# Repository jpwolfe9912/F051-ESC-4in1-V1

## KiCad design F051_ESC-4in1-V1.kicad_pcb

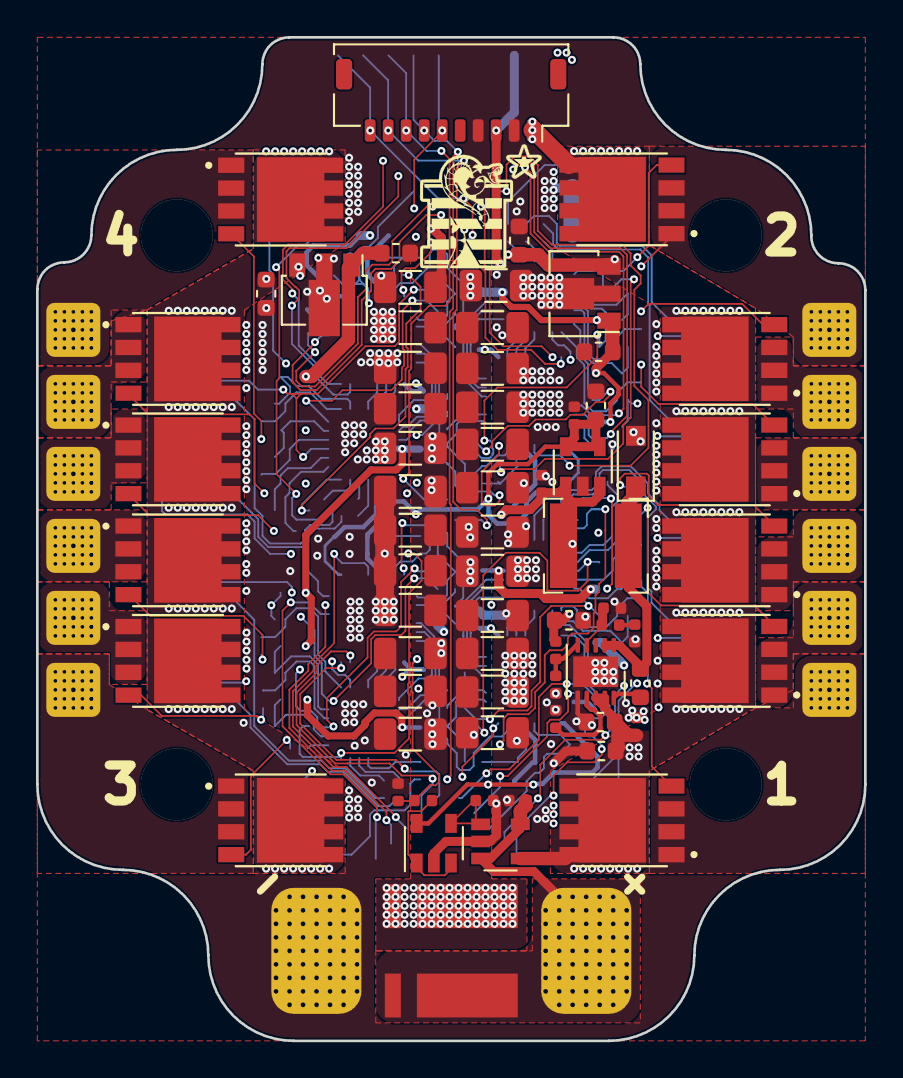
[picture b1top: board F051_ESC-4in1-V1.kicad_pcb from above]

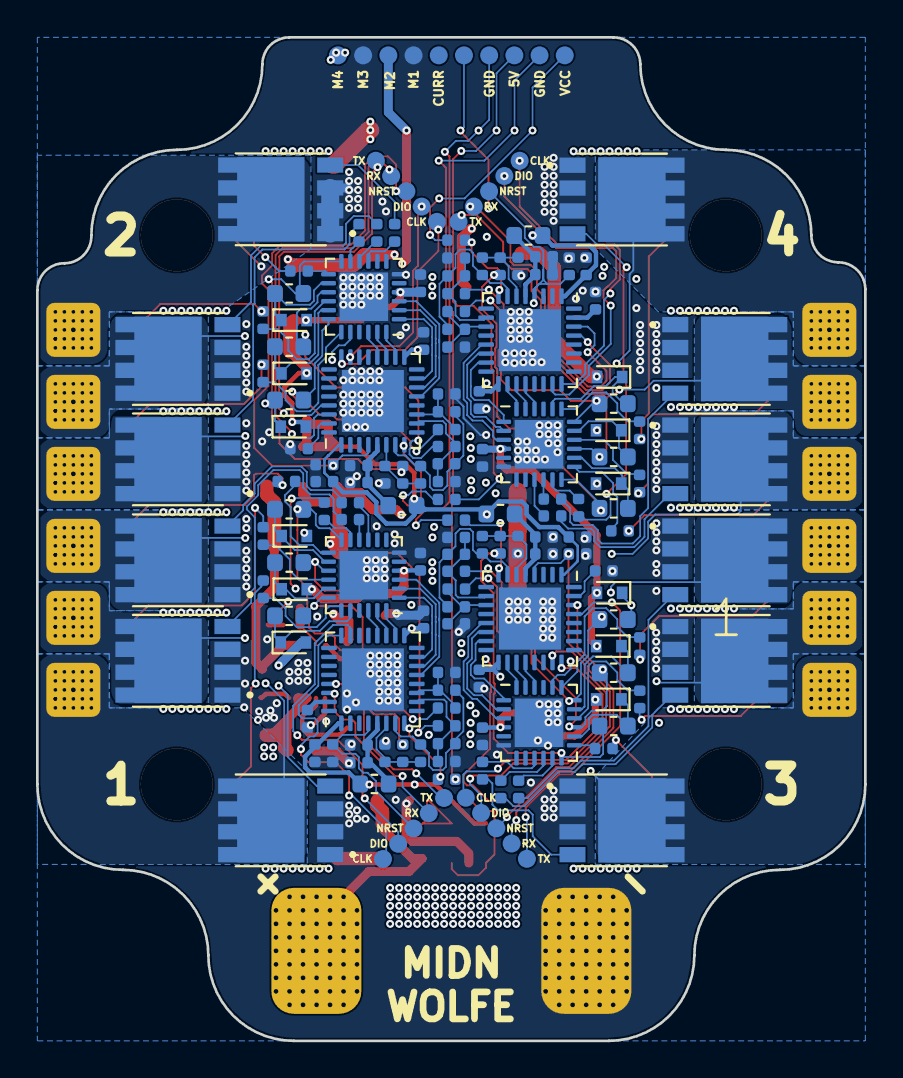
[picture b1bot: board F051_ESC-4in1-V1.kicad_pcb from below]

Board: 4 copper layers, 46.0 x 55.8 mm, 222 parts (147 on the bottom side), 164 nets.

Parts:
C1, C23, C27, C32, C41: 10nF; C_0402_1005Metric
C2, C22, C28, C33, C42: 1uF; C_0402_1005Metric
C3, C6, C7, C9, C11, C12, C29, C30, C31, C34, C35, C36, C37, C43, C44, C45, C46, C74: 0.1uF; C_0402_1005Metric
C4, C68: 0.33uF; C_0603_1608Metric
C5, C10, C13, C14, C15, C25, C26, C38, C39, C40, C47, C48, C49, C69, C70: 0.1uF; C_0603_1608Metric
C8: 3.3nF; C_0402_1005Metric
C16, C17, C18, C19, C20, C21, C50, C51, C52, C53, C54, C55, C56, C57, C58, C59, C60, C61, C62, C63, C64, C65, C66, C67: 0.1uF; C_1206_3216Metric
C24, C72, C73: 2.2uF; C_0603_1608Metric
C71: 22uF; C_0603_1608Metric
C75: 560pF; C_0402_1005Metric
C76: 2pF; C_0402_1005Metric
D1, D2, D3, D4, D5, D6, D7, D8, D9, D10, D11, D12: 250V; D_SOD-523
D13: 50V, 2A; D_SOD-123F
FB1, FB2, FB3, FB4: 100@100MHz; L_0603_1608Metric
H1, H2, H3, H4: MountingHole_Pad; MountingHole_4in1ESC
J1: Conn_01x02; Conn_PowerPad_4in1
J2: Conn_01x10; JST_SHL_SM10B-SHLS-TF_1x10-1MP_P1.00mm_Horizontal
J3, J4, J5, J7: Conn_01x05; Conn_Debug
J6, J8, J11, J14: Conn_01x03; Conn_MotorPhase
J9: Conn_01x10; Conn_FC_Solder_10
L1: L_Small; L_Bourns-SRN5020
Q1, Q2, Q3, Q4, Q5, Q6, Q7, Q8, Q9, Q10, Q11, Q12, Q13, Q14, Q15, Q16, Q17, Q18, Q19, Q20, Q21, Q22, Q23, Q24: TPHR8504PL
R1: 0m50; R_Shunt_Vishay_WSLP2726
R2: 60k; R_0402_1005Metric
R3: 500; R_0402_1005Metric
R4, R5, R6, R18, R19, R20, R21, R22, R23, R24, R25, R26, R49, R50, R51, R52, R53, R54, R66, R67, R68, R69, R70, R71: 10; R_0402_1005Metric
R7, R8, R9, R10, R12, R13, R27, R28, R29, R30, R32, R33, R38, R39, R40, R41, R43, R44, R55, R56, R57, R58, R60, R61: 10k; R_0402_1005Metric
R11, R14, R15, R16, R17, R31, R34, R35, R36, R37, R42, R45, R46, R47, R48, R59, R62, R63, R64, R65: 1k; R_0402_1005Metric
R73: 20k; R_0402_1005Metric
R74: 3.8k; R_0402_1005Metric
R76: 200k; R_0402_1005Metric
R77: 68k; R_0402_1005Metric
U1, U8, U9, U11: STM32F051K6Ux; QFN-32-1EP_5x5mm_P0.5mm_EP3.45x3.45mm
U2, U6, U10, U12: FD6288Q; QFN-24-1EP_4x4mm_P0.5mm_EP2.7x2.7mm
U3, U13: L78L12_SOT89; SOT-89-3
U4: LP2985-3.3; SOT-23-5
U5: INA139; SOT-23-5
U7: OPA340NA; SOT-23-5
U14: MP4560_QFN10; DFN-10-1EP_3x3mm_P0.5mm_EP1.7x2.5mm

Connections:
+3.3VA_1: C1.1, C2.1, FB1.1, U1.5
+3.3VA_2: C27.1, C28.1, FB2.1, U8.5
+3.3VA_3: C32.1, C33.1, FB3.1, U9.5
+3.3VA_4: C41.1, C42.1, FB4.1, U11.5
+3V3: C3.1, C6.1, C23.1, C24.1, C29.1, C30.1, C34.1, C35.1, C43.1, C44.1, FB1.2, FB2.2, FB3.2, FB4.2, U1.1, U1.17, U4.4, U4.5, U7.5, U8.1, U8.17, U9.1, U9.17, U11.1, U11.17
+5V: C22.1, C71.1, J2.3, J9.3, L1.2, R73.1, U4.1, U4.3
+12V_1: C37.1, C46.1, C69.1, D7.2, D8.2, D9.2, D10.2, D11.2, D12.2, U10.4, U12.4, U13.1
+12V_2: C5.1, C9.1, C12.1, D1.2, D2.2, D3.2, D4.2, D5.2, D6.2, U2.4, U3.1, U6.4
/Curent Sense/CURR: C8.2, J2.6, J9.6, R3.1
/MCU 1/BOOT0: R17.1, U1.31
/MCU 1/HIN1: U1.18, U2.24
/MCU 1/HIN2: U1.19, U2.23
/MCU 1/LIN1: U1.15, U2.1
/MCU 1/LIN2: U1.14, U2.2
/MCU 1/LIN3: U1.13, U2.3
/MCU 1/NRST: C11.1, J3.3, U1.4
/MCU 1/PhaseA: C13.2, J6.3, Q1.1, Q1.2, Q1.3, Q2.5, Q2.6, Q2.7, Q2.8, Q2.9, R7.2, U2.18
/MCU 1/PhaseB: C14.2, J6.2, Q3.1, Q3.2, Q3.3, Q4.5, Q4.6, Q4.7, Q4.8, Q4.9, R9.2, U2.15
/MCU 1/PhaseC: C15.2, J6.1, Q5.1, Q5.2, Q5.3, Q6.5, Q6.6, Q6.7, Q6.8, Q6.9, R12.2, U2.12
/MCU 1/SWCLK: J3.1, U1.24
/MCU 1/SWDIO: J3.2, U1.23
/MCU 1/SenseA: R7.1, R8.1, R14.2, U1.11
/MCU 1/SenseB: R9.1, R10.1, R15.2, U1.10
/MCU 1/SenseC: R12.1, R13.1, R16.2, U1.6
/MCU 1/SenseCOM: R8.2, R10.2, R13.2, U1.7
/MCU 1/USART1_RX: J3.4, U1.30
/MCU 1/USART1_TX: J3.5, U1.29
/MCU 2/BOOT0: R37.1, U8.31
/MCU 2/HIN1: U6.24, U8.18
/MCU 2/HIN2: U6.23, U8.19
/MCU 2/LIN1: U6.1, U8.15
/MCU 2/LIN2: U6.2, U8.14
/MCU 2/LIN3: U6.3, U8.13
/MCU 2/NRST: C31.1, J5.3, U8.4
/MCU 2/PhaseA: C10.2, J8.3, Q7.1, Q7.2, Q7.3, Q8.5, Q8.6, Q8.7, Q8.8, Q8.9, R27.2, U6.18
/MCU 2/PhaseB: C25.2, J8.2, Q9.1, Q9.2, Q9.3, Q10.5, Q10.6, Q10.7, Q10.8, Q10.9, R29.2, U6.15
/MCU 2/PhaseC: C26.2, J8.1, Q11.1, Q11.2, Q11.3, Q12.5, Q12.6, Q12.7, Q12.8, Q12.9, R32.2, U6.12
/MCU 2/SWCLK: J5.1, U8.24
/MCU 2/SWDIO: J5.2, U8.23
/MCU 2/SenseA: R27.1, R28.1, R34.2, U8.11
/MCU 2/SenseB: R29.1, R30.1, R35.2, U8.10
/MCU 2/SenseC: R32.1, R33.1, R36.2, U8.6
/MCU 2/SenseCOM: R28.2, R30.2, R33.2, U8.7
/MCU 2/USART1_RX: J5.4, U8.30
/MCU 2/USART1_TX: J5.5, U8.29
/MCU 3/BOOT0: R48.1, U9.31
/MCU 3/HIN1: U9.18, U10.24
/MCU 3/HIN2: U9.19, U10.23
/MCU 3/LIN1: U9.15, U10.1
/MCU 3/LIN2: U9.14, U10.2
/MCU 3/LIN3: U9.13, U10.3
/MCU 3/NRST: C36.1, J4.3, U9.4
/MCU 3/PhaseA: C38.2, J11.3, Q13.1, Q13.2, Q13.3, Q14.5, Q14.6, Q14.7, Q14.8, Q14.9, R38.2, U10.18
/MCU 3/PhaseB: C39.2, J11.2, Q15.1, Q15.2, Q15.3, Q16.5, Q16.6, Q16.7, Q16.8, Q16.9, R40.2, U10.15
/MCU 3/PhaseC: C40.2, J11.1, Q17.1, Q17.2, Q17.3, Q18.5, Q18.6, Q18.7, Q18.8, Q18.9, R43.2, U10.12
/MCU 3/SWCLK: J4.1, U9.24
/MCU 3/SWDIO: J4.2, U9.23
/MCU 3/SenseA: R38.1, R39.1, R45.2, U9.11
/MCU 3/SenseB: R40.1, R41.1, R46.2, U9.10
/MCU 3/SenseC: R43.1, R44.1, R47.2, U9.6
/MCU 3/SenseCOM: R39.2, R41.2, R44.2, U9.7
/MCU 3/USART1_RX: J4.4, U9.30
/MCU 3/USART1_TX: J4.5, U9.29
/MCU 4/BOOT0: R65.1, U11.31
/MCU 4/HIN1: U11.18, U12.24
/MCU 4/HIN2: U11.19, U12.23
/MCU 4/LIN1: U11.15, U12.1
/MCU 4/LIN2: U11.14, U12.2
/MCU 4/LIN3: U11.13, U12.3
/MCU 4/NRST: C45.1, J7.3, U11.4
/MCU 4/PhaseA: C47.2, J14.3, Q19.1, Q19.2, Q19.3, Q20.5, Q20.6, Q20.7, Q20.8, Q20.9, R55.2, U12.18
/MCU 4/PhaseB: C48.2, J14.2, Q21.1, Q21.2, Q21.3, Q22.5, Q22.6, Q22.7, Q22.8, Q22.9, R57.2, U12.15
/MCU 4/PhaseC: C49.2, J14.1, Q23.1, Q23.2, Q23.3, Q24.5, Q24.6, Q24.7, Q24.8, Q24.9, R60.2, U12.12
/MCU 4/SWCLK: J7.1, U11.24
/MCU 4/SWDIO: J7.2, U11.23
/MCU 4/SenseA: R55.1, R56.1, R62.2, U11.11
/MCU 4/SenseB: R57.1, R58.1, R63.2, U11.10
/MCU 4/SenseC: R60.1, R61.1, R64.2, U11.6
/MCU 4/SenseCOM: R56.2, R58.2, R61.2, U11.7
/MCU 4/USART1_RX: J7.4, U11.30
/MCU 4/USART1_TX: J7.5, U11.29
/MOSFET Driver 1/HIN1: U1.20, U2.22
/MOSFET Driver 1/HO1: R18.2, U2.19
/MOSFET Driver 1/HO2: R20.2, U2.16
/MOSFET Driver 1/HO3: R23.2, U2.13
/MOSFET Driver 1/LO1: R19.2, U2.11
/MOSFET Driver 1/LO2: R21.2, U2.10
/MOSFET Driver 1/LO3: R24.2, U2.9
/MOSFET Driver 1/VB1: C13.1, D2.1, U2.20
/MOSFET Driver 1/VB2: C14.1, D3.1, U2.17
/MOSFET Driver 1/VB3: C15.1, D4.1, U2.14
/MOSFET Driver 2/HIN1: U6.22, U8.20
/MOSFET Driver 2/HO1: R4.2, U6.19
/MOSFET Driver 2/HO2: R6.2, U6.16
/MOSFET Driver 2/HO3: R25.2, U6.13
/MOSFET Driver 2/LO1: R5.2, U6.11
/MOSFET Driver 2/LO2: R22.2, U6.10
/MOSFET Driver 2/LO3: R26.2, U6.9
/MOSFET Driver 2/VB1: C10.1, D1.1, U6.20
/MOSFET Driver 2/VB2: C25.1, D5.1, U6.17
/MOSFET Driver 2/VB3: C26.1, D6.1, U6.14
/MOSFET Driver 3/HIN1: U9.20, U10.22
/MOSFET Driver 3/HO1: R49.2, U10.19
/MOSFET Driver 3/HO2: R51.2, U10.16
/MOSFET Driver 3/HO3: R53.2, U10.13
/MOSFET Driver 3/LO1: R50.2, U10.11
/MOSFET Driver 3/LO2: R52.2, U10.10
/MOSFET Driver 3/LO3: R54.2, U10.9
/MOSFET Driver 3/VB1: C38.1, D7.1, U10.20
/MOSFET Driver 3/VB2: C39.1, D8.1, U10.17
/MOSFET Driver 3/VB3: C40.1, D9.1, U10.14
/MOSFET Driver 4/HIN1: U11.20, U12.22
/MOSFET Driver 4/HO1: R66.2, U12.19
/MOSFET Driver 4/HO2: R68.2, U12.16
/MOSFET Driver 4/HO3: R70.2, U12.13
/MOSFET Driver 4/LO1: R67.2, U12.11
/MOSFET Driver 4/LO2: R69.2, U12.10
/MOSFET Driver 4/LO3: R71.2, U12.9
/MOSFET Driver 4/VB1: C47.1, D10.1, U12.20
/MOSFET Driver 4/VB2: C48.1, D11.1, U12.17
/MOSFET Driver 4/VB3: C49.1, D12.1, U12.14
/PWM_1: J2.7, J9.7, R11.2
/PWM_2: J2.8, J9.8, R31.2
/PWM_3: J2.9, J9.9, R42.2
/PWM_4: J2.10, J9.10, R59.2
GND: C1.2, C2.2, C3.2, C4.2, C5.2, C6.2, C7.1, C8.1, C9.2, C11.2, C12.2, C16.1, C17.1, C18.1, C19.1, C20.1, C21.1, C22.2, C23.2, C24.2, C27.2, C28.2, C29.2, C30.2, C31.2, C32.2, C33.2, C34.2, C35.2, C36.2, C37.2, C41.2, C42.2, C43.2, C44.2, C45.2, C46.2, C50.1, C51.1, C52.1, C53.1, C54.1, C55.1, C56.1, C57.1, C58.1, C59.1, C60.1, C61.1, C62.1, C63.1, C64.1, C65.1, C66.1, C67.1, C68.2, C69.2, C71.2, C72.2, C73.2, C74.2, C76.2, D13.2, H1.1, H2.1, H3.1, H4.1, J1.2, J2.2, J2.4, J9.2, J9.4, Q2.1, Q2.2, Q2.3, Q4.1, Q4.2, Q4.3, Q6.1, Q6.2, Q6.3, Q8.1, Q8.2, Q8.3, Q10.1, Q10.2, Q10.3, Q12.1, Q12.2, Q12.3, Q14.1, Q14.2, Q14.3, Q16.1, Q16.2, Q16.3, Q18.1, Q18.2, Q18.3, Q20.1, Q20.2, Q20.3, Q22.1, Q22.2, Q22.3, Q24.1, Q24.2, Q24.3, R2.2, R14.1, R15.1, R16.1, R17.2, R34.1, R35.1, R36.1, R37.2, R45.1, R46.1, R47.1, R48.2, R62.1, R63.1, R64.1, R65.2, R74.2, R76.2, R77.2, U1.33, U2.6, U2.25, U3.2, U4.2, U5.2, U6.6, U6.25, U7.2, U8.33, U9.33, U10.6, U10.25, U11.33, U12.6, U12.25, U13.2, U14.6
unnamed: C70.1, D13.1, L1.1, U14.1, U14.2
unnamed: C70.2, U14.10
unnamed: C75.1, C76.1, U14.4
unnamed: C75.2, R77.1
unnamed: Q1.4, R18.1
unnamed: Q2.4, R19.1
unnamed: Q3.4, R20.1
unnamed: Q4.4, R21.1
unnamed: Q5.4, R23.1
unnamed: Q6.4, R24.1
unnamed: Q7.4, R4.1
unnamed: Q8.4, R5.1
unnamed: Q9.4, R6.1
unnamed: Q10.4, R22.1
unnamed: Q11.4, R25.1
unnamed: Q12.4, R26.1
unnamed: Q13.4, R49.1
unnamed: Q14.4, R50.1
unnamed: Q15.4, R51.1
unnamed: Q16.4, R52.1
unnamed: Q17.4, R53.1
unnamed: Q18.4, R54.1
unnamed: Q19.4, R66.1
unnamed: Q20.4, R67.1
unnamed: Q21.4, R68.1
unnamed: Q22.4, R69.1
unnamed: Q23.4, R70.1
unnamed: Q24.4, R71.1
unnamed: R2.1, U5.1, U7.4
unnamed: R3.2, U7.1, U7.3
unnamed: R11.1, U1.8
unnamed: R31.1, U8.8
unnamed: R42.1, U9.8
unnamed: R59.1, U11.8
unnamed: R73.2, R74.1, U14.5
unnamed: R76.1, U14.7
VCC: C7.2, J1.1, R1.1, U5.3, U5.5
VCC_Shunt: C4.1, C16.2, C17.2, C18.2, C19.2, C20.2, C21.2, C50.2, C51.2, C52.2, C53.2, C54.2, C55.2, C56.2, C57.2, C58.2, C59.2, C60.2, C61.2, C62.2, C63.2, C64.2, C65.2, C66.2, C67.2, C68.1, C72.1, C73.1, C74.1, J2.1, J9.1, Q1.5, Q1.6, Q1.7, Q1.8, Q1.9, Q3.5, Q3.6, Q3.7, Q3.8, Q3.9, Q5.5, Q5.6, Q5.7, Q5.8, Q5.9, Q7.5, Q7.6, Q7.7, Q7.8, Q7.9, Q9.5, Q9.6, Q9.7, Q9.8, Q9.9, Q11.5, Q11.6, Q11.7, Q11.8, Q11.9, Q13.5, Q13.6, Q13.7, Q13.8, Q13.9, Q15.5, Q15.6, Q15.7, Q15.8, Q15.9, Q17.5, Q17.6, Q17.7, Q17.8, Q17.9, Q19.5, Q19.6, Q19.7, Q19.8, Q19.9, Q21.5, Q21.6, Q21.7, Q21.8, Q21.9, Q23.5, Q23.6, Q23.7, Q23.8, Q23.9, R1.2, U3.3, U5.4, U13.3, U14.8, U14.9

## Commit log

2021-03-16 Adding new files
2021-03-16 Added the rest of the phases and their associated components
2021-03-16 Updated Design
2021-03-16 Added a test circuit to figure out best configuration
2021-03-17 More design changes
2021-03-17 Circuit added to board
2021-03-17 Finalized back layer and added FETs to front layer
2021-03-17 Added pads for battery and debugging
2021-03-17 Addition of 5V Regulator
2021-03-17 Added more planes, rearranged 5V circuit
2021-03-17 Added 3V3 regulator and connected it to rest of board
2021-03-18 Connected a lot of stuff
2021-03-18 A few more traces laid out
2021-03-18 Rerouted a bunch of the phase traces so they are shorter
2021-03-18 More routing of phase traces
2021-03-18 A lot more traces added
2021-03-19 Routed a lot more stuff. Just some more GND and VCC vias to add
2021-03-19 More GND and VCC vias and planes added. Moved around some sense resistors to expose GND
2021-03-19 Finished all traces and vias
2021-03-19 Added PNGs
2021-03-19 Added more PNGs
2021-03-19 Deleted some extra files
2021-03-19 Moved around some traces to create bigger fills
2021-03-19 Changed shunt resistor footprint and changed edge cuts to accomodate larger size
2021-03-20 Some graphical additions
2021-03-20 Changed input filtering caps to 47uF from 0.1uF
2021-03-20 Updated PNGS
2021-03-20 Adjusted some of the fills to match the grid
2021-03-22 Cleared front layer and rearranging
